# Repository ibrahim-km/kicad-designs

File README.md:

# kicad-designs
PCB designs created using KiCad, including power electronics and embedded hardware projects.

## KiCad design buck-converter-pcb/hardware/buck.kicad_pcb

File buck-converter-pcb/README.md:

# 48V to 12V Buck Converter PCB

A high-efficiency SMPS buck converter designed in KiCad using the LM2576HVS-12 regulator to step down 48V DC to a regulated 12V DC output.

## Status

Completed

## Tools Used

- KiCad
- LM2576HVS-12
- Power Electronics Design
- PCB Layout Design

## Project Images

### Schematic

### PCB Layout

### 3D Render

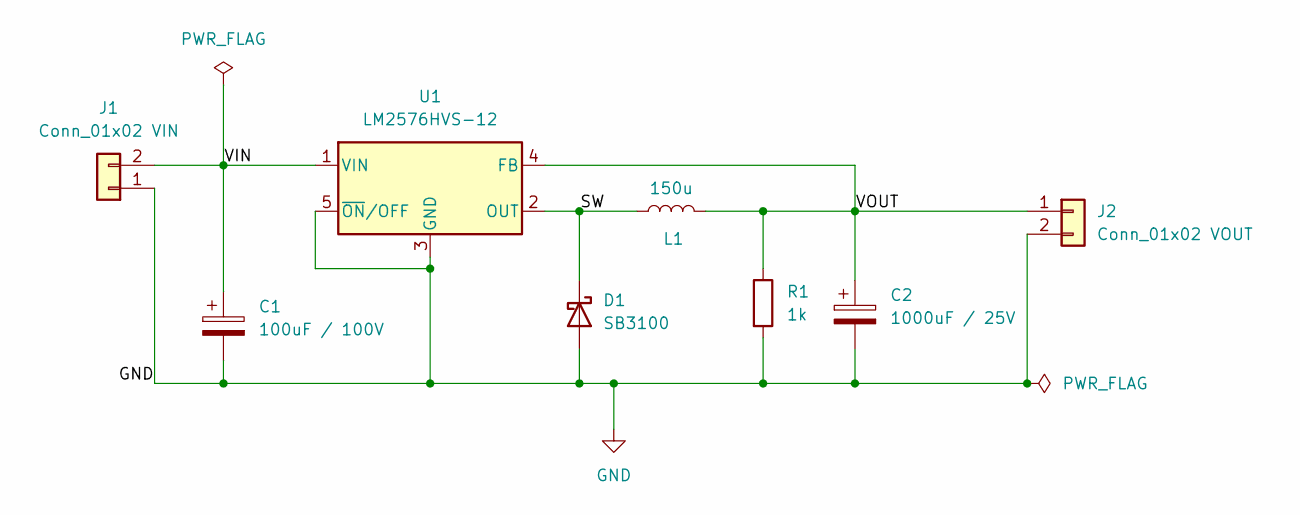
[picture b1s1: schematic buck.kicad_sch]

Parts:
C1: 100uF / 100V; CP_Radial_D10.0mm_P5.00mm
C2: 1000uF / 25V; CP_Radial_D10.0mm_P5.00mm
D1: SB3100; D_DO-201AD_P15.24mm_Horizontal
J1: Conn_01x02 VIN; TerminalBlock_Phoenix_MKDS-1,5-2-5.08_1x02_P5.08mm_Horizont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
J2: Conn_01x02 VOUT; TerminalBlock_Phoenix_MKDS-1,5-2-5.08_1x02_P5.08mm_Horizont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
L1: 150u; L_Toroid_Vertical_L10.0mm_W5.0mm_P5.08mm
R1: 1k; R_Axial_DIN0207_L6.3mm_D2.5mm_P10.16mm_Horizontal
U1: LM2576HVS-12; TO-220-5_Vertical

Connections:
/SW: D1.1 (K), L1.1, U1.2 (OUT)
/VIN: C1.1, J1.2, U1.1 (VIN)
/VOUT: C2.1, J2.1, L1.2, R1.1, U1.4 (FB)
GND: C1.2, C2.2, D1.2 (A), J1.1, J2.2, R1.2, U1.3 (GND), U1.5 (~ON/OFF)

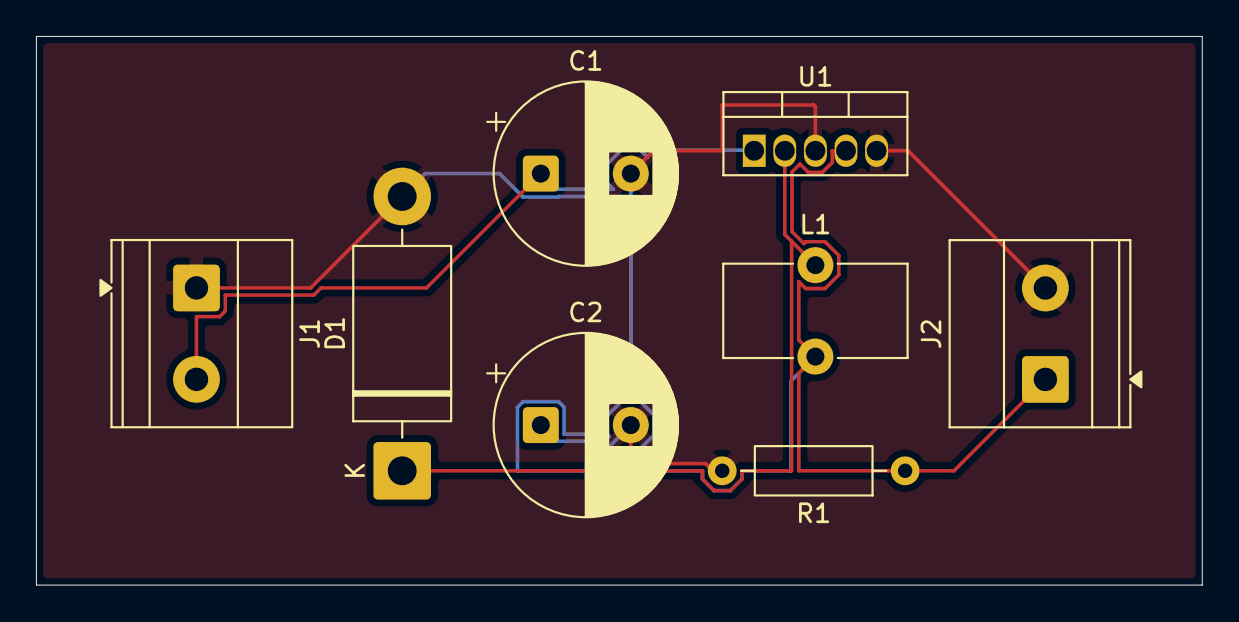
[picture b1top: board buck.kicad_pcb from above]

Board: 2 copper layers, 64.8 x 30.5 mm, 8 parts (0 on the bottom side), 4 nets.

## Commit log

2026-06-23 Rename buck-converter-pcb/pcb-layout.png.png to buck-converter-pcb/images/pcb-layout.png.png
2026-06-23 Rename buck-converter-pcb/schematic.png.png to buck-converter-pcb/images/schematic.png.png
2026-06-23 Rename buck-converter-pcb/3d-view.png.png to buck-converter-pcb/images/3d-view.png.png
2026-06-23 Rename buck-converter-pcb/buck.kicad_pcb to buck-converter-pcb/hardware/buck.kicad_pcb
2026-06-23 Rename buck-converter-pcb/buck.kicad_pro to buck-converter-pcb/hardware/buck.kicad_pro
2026-06-23 Rename buck-converter-pcb/buck.kicad_sch to buck-converter-pcb/hardware/buck.kicad_sch
2026-06-23 Rename buck-converter-pcb/design_report.pdf to buck-converter-pcb/docs/design-report.pdf
2026-06-23 Rename design-report.pdf to buck-converter-report.pdf
